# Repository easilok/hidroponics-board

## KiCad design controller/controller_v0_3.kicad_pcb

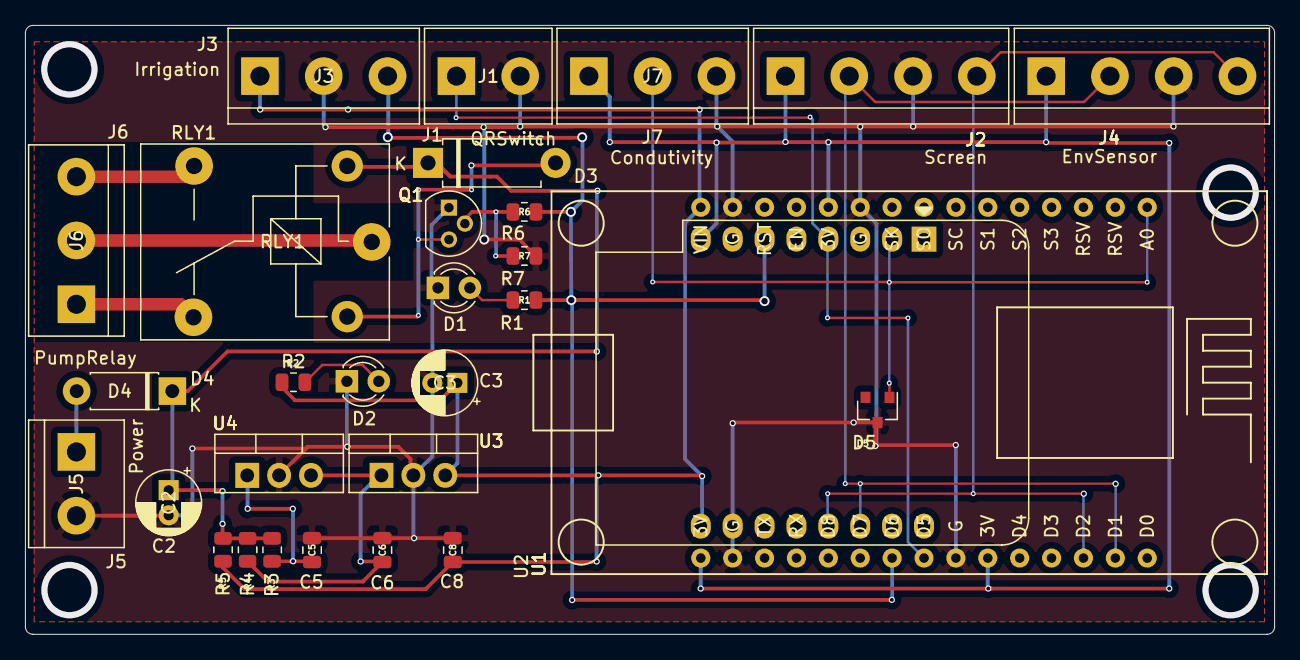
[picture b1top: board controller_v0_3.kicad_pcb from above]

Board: 2 copper layers, 99.5 x 48.5 mm, 30 parts (0 on the bottom side), 19 nets.

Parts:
C2, C3: 0.1u; CP_Radial_D5.0mm_P2.00mm
C5, C6: 0.33u; C_0805_2012Metric
C8: 0.1u; C_0805_2012Metric
D1, D2: LED; LED_D3.0mm
D3: D; D_DO-15_P10.16mm_Horizontal
D4: D; D_DO-41_SOD81_P7.62mm_Horizontal
D5: D_Zener_x2_ACom_AKK; SOT-23
J1: QRSwitch; TerminalBlock_bornier-2_P5.08mm
J2: Screen; TerminalBlock_bornier-4_P5.08mm
J3: Irrigation; TerminalBlock_bornier-3_P5.08mm
J4: EnvSensor; TerminalBlock_bornier-4_P5.08mm
J5: Power; TerminalBlock_bornier-2_P5.08mm
J6: PumpRelay; TerminalBlock_bornier-3_P5.08mm
J7: Condutivity; TerminalBlock_bornier-3_P5.08mm
Q1: MPS2222; TO-92
R1, R2: 10K; R_0805_2012Metric
R3, R4, R5: 0; R_0805_2012Metric
R6, R7: 1K; R_0805_2012Metric
RLY1: AZ943-1CH-12DE; Relay_SPDT_ZETTLER_AZ943_Series_Form_C
U1: WeMos_D1_mini; WEMOS_D1_mini_light
U2: NodeMCU_ESP12E; NodeMCU1.0_12-E
U3: LM7805_TO220; TO-220-3_Vertical
U4: LM7809_TO220; TO-220-3_Vertical

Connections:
+5V: C3.1, C8.1, J3.1, R2.1, R5.2, U1.9, U2.15, U3.3
/+3V3: J2.1, J4.1, J7.1, U1.8, U2.11, U2.16, U2.25
/COND_SENSOR: D5.1, J7.2, U1.2, U2.1
/I2C_SCL: J2.2, J4.2, U1.14, U2.29
/I2C_SDA: J2.4, J4.4, U1.13, U2.28
/POWER_INPUT: D4.2, J5.1
/POWER_Vin: C2.1, D3.1, D4.1, R3.1, R4.1, R5.1, RLY1.2
/QR_SWITCH: J1.1, U1.4, U2.23
/RELAY_C: J6.2, RLY1.1
/RELAY_CMD: J3.3, R1.1, R6.2, U1.6, U2.22
/RELAY_NC: J6.1, RLY1.4
/RELAY_NO: J6.3, RLY1.3
/Vin_5V: C6.1, R4.2, U3.1, U4.3
/Vin_9V: C5.1, R3.2, U4.1
GND: C2.2, C3.2, C5.2, C6.2, C8.2, D1.1, D2.1, D5.3, J1.2, J2.3, J3.2, J4.3, J5.2, J7.3, Q1.1, R7.1, U1.10, U2.10, U2.14, U2.17, U2.24, U3.2, U4.2
unnamed: D1.2, R1.2
unnamed: D2.2, R2.2
unnamed: D3.2, Q1.3, RLY1.5
unnamed: Q1.2, R6.1, R7.2

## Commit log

2021-06-04 Wemos D1 implemented
2021-06-17 Released to production V0.2
2021-06-18 Added BOM
2021-07-08 Production version. First iteration for correction
2022-04-29 Added version 0.3 with hardware corrections
